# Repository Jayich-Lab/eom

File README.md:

# Electro-optic Modulator

The design for this project is based heavily on work done in the [Will Lab](https://www.will-lab.com/) that they generously shared with us.

## EO Crystal 

We chose Lithium niobate (LiNbO<sub>3</sub>). It has a good Pockels effect, so we can minimize the input voltage to achieve the required modulation depth.
#### Relationship between the index of refraction, the electro-optic tensor, and the electric field:

<div align="center"><img width="300"  src="https://latex.codecogs.com/png.latex?\dpi{300}&space;\begin{pmatrix}&space;\Delta(\frac{1}{n^{2}})_{1}\\&space;\Delta(\frac{1}{n^{2}})_{2}\\&space;\Delta(\frac{1}{n^{2}})_{3}\\&space;\Delta(\frac{1}{n^{2}})_{4}\\&space;\Delta(\frac{1}{n^{2}})_{5}\\&space;\Delta(\frac{1}{n^{2}})_{6}&space;\end{pmatrix}=&space;\begin{pmatrix}&space;r_{11}&space;&r_{12}&space;&r_{13}&space;\\&space;r_{21}&space;&r_{22}&space;&r_{23}&space;\\&space;r_{31}&space;&r_{32}&space;&r_{33}&space;\\&space;r_{41}&space;&r_{42}&space;&r_{43}&space;\\&space;r_{51}&space;&r_{52}&space;&r_{53}&space;\\&space;r_{61}&space;&r_{62}&space;&r_{63}&space;\end{pmatrix}\begin{pmatrix}&space;E_x\\&space;E_y\\&space;E_z&space;\end{pmatrix}" title="\begin{pmatrix} \Delta(\frac{1}{n^{2}})_{1}\\ \Delta(\frac{1}{n^{2}})_{2}\\ \Delta(\frac{1}{n^{2}})_{3}\\ \Delta(\frac{1}{n^{2}})_{4}\\ \Delta(\frac{1}{n^{2}})_{5}\\ \Delta(\frac{1}{n^{2}})_{6} \end{pmatrix}= \begin{pmatrix} r_{11} &r_{12} &r_{13} \\ r_{21} &r_{22} &r_{23} \\ r_{31} &r_{32} &r_{33} \\ r_{41} &r_{42} &r_{43} \\ r_{51} &r_{52} &r_{53} \\ r_{61} &r_{62} &r_{63} \end{pmatrix}\begin{pmatrix} E_x\\ E_y\\ E_z \end{pmatrix}" /></div>

#### Electro-optic tensor of LiNbO<sub>3</sub> -- 3m(C3v) point group:
<div align="center"> </div>  

#### Electro-optic Coefficient for Lithium Niobate (LiNbO<sub>3</sub>):

Electro-optic Coefficient | Value (pm/V) | 
:---: | :---: | 
r<sub>13</sub> | 9.6 
r<sub>22</sub> | 6.8
r<sub>33</sub> | 30.9 
r<sub>42</sub> | 32.6  

Taken from Boyd, 2003. This is within a [margin of error](http://www.lambdaphoto.co.uk/pdfs/Inrad_datasheet_LNB.pdf).

## Required voltage for changing a π phase

The "cut" of a crystal is the direction light is meant to propogate through it, e.g. Y-Cut means light will travel in the Y direction of crystal (where the X, Y, Z directions are specified by the crystal geometry). The voltage required for a pi phase shift is determined by the cut.

Applied electric field in Z direction, wave propagates in Y direction (Y-Cut):

<div align="center"></div>  

<br/><br/>

Applied electric field in Y direction, wave propagates in Z direction (Z-Cut):
<div align="center"></div>

#### Refractive Index for Lithium Niobate (LiNbO<sub>3</sub>) at different wavelengths

Value for n<sub>e</sub> | Value for n<sub>o</sub>  | Laser wavelength 
:---: | :---: | :---:
2.2666 | 2.3650 | 468nm
2.2342 | 2.3232 | 532nm
2.1875 | 2.2715 | 708nm
2.1845 | 2.2680 | 728nm
2.1702 | 2.2491 | 852nm
2.156 | 2.232 | 1064nm

---

## Final Design

We used Y-cut lithium niobate as our EO crystal. The bandwidth needed was 400nm-1100nm. We used different AR coatings to cover this range, one from 400-700nm and one from 700-1100nm. The crystal is 3mm x 3mm x 30mm, where one face is 3mm x 3mm.

#### The voltage needed across the EO crystal is:

λ( in meter ) | V<sub>π</sub> ( in volts )
:---: | :---: 
468 × 10<sup>-9</sup> | 201 V
532 × 10<sup>-9</sup> | 237 V
708 × 10<sup>-9</sup> | 335.65 V
852 × 10<sup>-9</sup> | 412 V
1064 × 10<sup>-9</sup> | 524.325 V

---

## Resonant circuit
We used a resonant circuit to minimize the input voltage which keeps the device safe to operate and avoids the extra effort of generating that high voltage.

The resonant frequency can be calculated:

<div align="center"></div>

We can use the usual parallel plate capacitor formula to calculate capacitance: 
<div align="center"></div>

Permittivity for Lithium Niobate is a tensor:
<div align="center"></div>

If we apply electric field in Z direction, we are going to use ε<sub>33</sub>

Parameter | Value | Description
:---: | :---: | :---: 
ε<sub>33</sub> | 0.2543 × 10<sup>-9</sup> | permittivity for lithium niobate (in F⋅m<sup>−1</sup>) (about 28~30 times larger than ε<sub>0</sub>)
A | 0.003 × 0.03 | area of two plates (in meters<sup>2</sup>)
d | 0.003 | distance between plates (in meters)
C | 7.629 × 10<sup>-12</sup> | Capacitance of the crystal 

We use impedance to calculate the V<sub>eom</sub> with respect to input voltage (V<sub>eom</sub> is the voltage difference of two plates between the EO crystal). V<sub>input</sub> is the applied voltage before the resonant circuit. R<sub>sma</sub> is the resistance of SMA RF connector. R<sub>load</sub> is the resistance for the circuit.

<div align="center"></div>

<div align="center"></div>

R<sub>sma</sub> = R<sub>load</sub> = 50 Ω  

C = 7.629 × 10<sup>-12</sup> (approximately)

We need a modulation frequency f = 10 MHz = 10<sup>7</sup> Hz so we need L ~ 33.2uH

Quality factor for this circuit (RLC circuit) Q ~ 20

So the the maximum voltage required to operate is ~25 V.

There will obviously be stray capacitance and other non-ideal effects. In practice our quality factor was about 6, and our resonant frequency was ~8.7MHz.

---

Parts used:

- [ ] [33.2uH inductor chip](https://www.digikey.com/product-detail/en/tdk-corporation/SLF7032T-330MR75-2PF/445-2005-1-ND/755412)
- [ ] [RF Connector (50ohm)](https://www.digikey.com/products/en?keywords=SMA-J-P-H-ST-EM1)
- [ ] (2) Indium foil (~4mm x 30mm)
- [ ] Lithium Niobate crystal
- [ ] [Delrin stock (to be milled, <13mm thickness is ideal)](https://www.mcmaster.com/plastics/wear-resistant-easy-to-machine-delrin-acetal-resin-sheets-bars-and-strips/thickness~1-2/)
- [ ] (8) 4-40 screws
- [ ] (8) 4-40 nuts
- [ ] (1) 8/32 screw
- [ ] [(4) Spring Washers](https://www.mcmaster.com/spring-washers/curved-disc-springs-6/id~0-135/)
- [ ] 8/32 compatible 1/2" optics post
- [ ] 1/2" optics post holder

---

# Instructions on how to build the EOM

First, mill the mount (generally any plastic works, but delrin was used for our EOMs). The mount design is in the repo as a fusion360 model and an stl/step model. 

Second, mill the top and bottom pcbs. Set a large clearance (20 mm) when milling them such that all copper visible on the board is for required lines. The eo crystal will be sandwiched in between the top and bottom pcbs, with the indium foil as a cushion. You should then solder the inductor and the sma connector onto the bottom pcb. It is advisable to solder the top pcb to the bottom for the ground connection at this point (leaving a reasonable amount of slack on the wire used).

You then want to take the eo crystal and gently place that between ~4mmx30mm strips of indium foil between the pcbs. (Make sure the side of the eo crystal used is correct!) Finally, screw everything together -- first screw the mount onto the 1/2" post, then the bottom pcb onto the mount, then the top pcb onto the mount (through the bottom pcb). Note that we use 4-40 screws with spring washers to do so.

You should be careful not to break the eo crystal when tightening. We found that not much force is required to make electrical contact. Note that our resonant frequency on the circuit was 8.7MHz, but you could change this by changing the inductance (were you in need of a different modulation frequency).

N.B. Try to make sure the screws are tightened somewhat evenly. Uneven pressures on the crystal are most likely to break it (fixed by spring washers).

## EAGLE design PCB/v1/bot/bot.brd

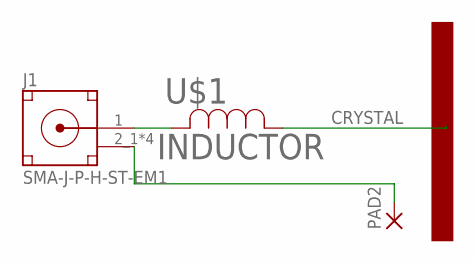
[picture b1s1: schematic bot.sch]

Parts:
J1: SMA-J-P-H-ST-EM1
PAD2: 2,54/1,1
U$1: INDUCTOR; IND_7030

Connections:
2L: J1.1 (SIGNAL), U$1.2
CRYSTAL: U$1.1
GND: J1.2_1 (GND), J1.2_2 (GND), J1.3_1 (GND), J1.3_2 (GND), PAD2.1

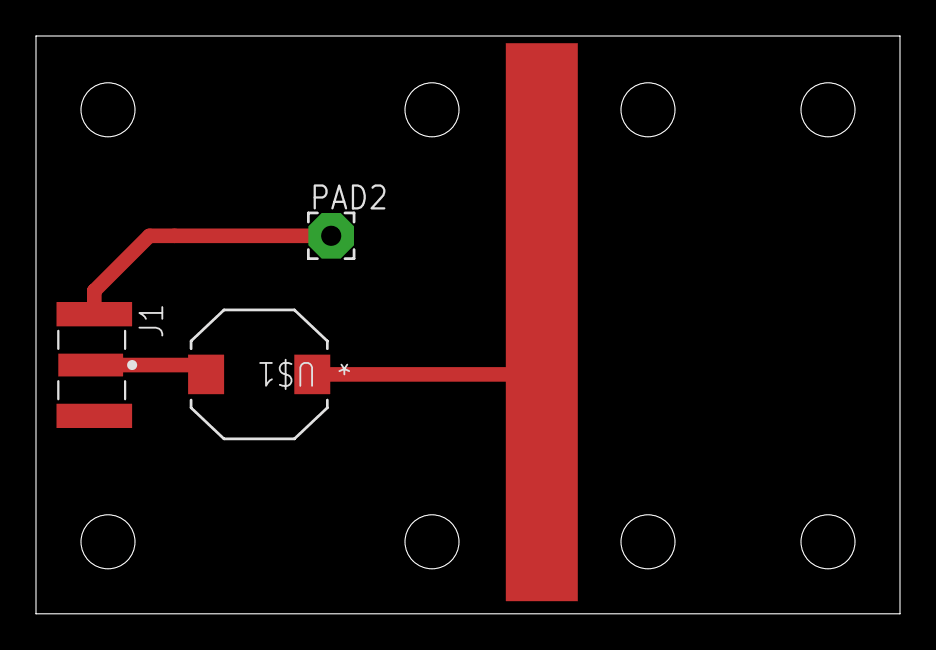
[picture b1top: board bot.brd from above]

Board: 2 copper layers, 48.0 x 32.1 mm, 3 parts (0 on the bottom side), 2 nets.

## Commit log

2019-02-21 add material for eom
2019-02-21 add root for pcb
2019-03-05 update formula for index of refraction
2019-03-07 Add some links
2019-04-03 top pcb board
2019-07-10 pcb_bottom finished
2019-07-11 add top board
2019-08-28 Create Design
2019-08-28 reorg
    reorg
2019-09-25 reorg
2019-09-25 pics
2020-07-09 update mount files
2020-07-09 kjihsbjxhkb
2020-07-10 8/32 head diameter
2020-09-03 voltage clarification
2021-08-05 eom pcb
